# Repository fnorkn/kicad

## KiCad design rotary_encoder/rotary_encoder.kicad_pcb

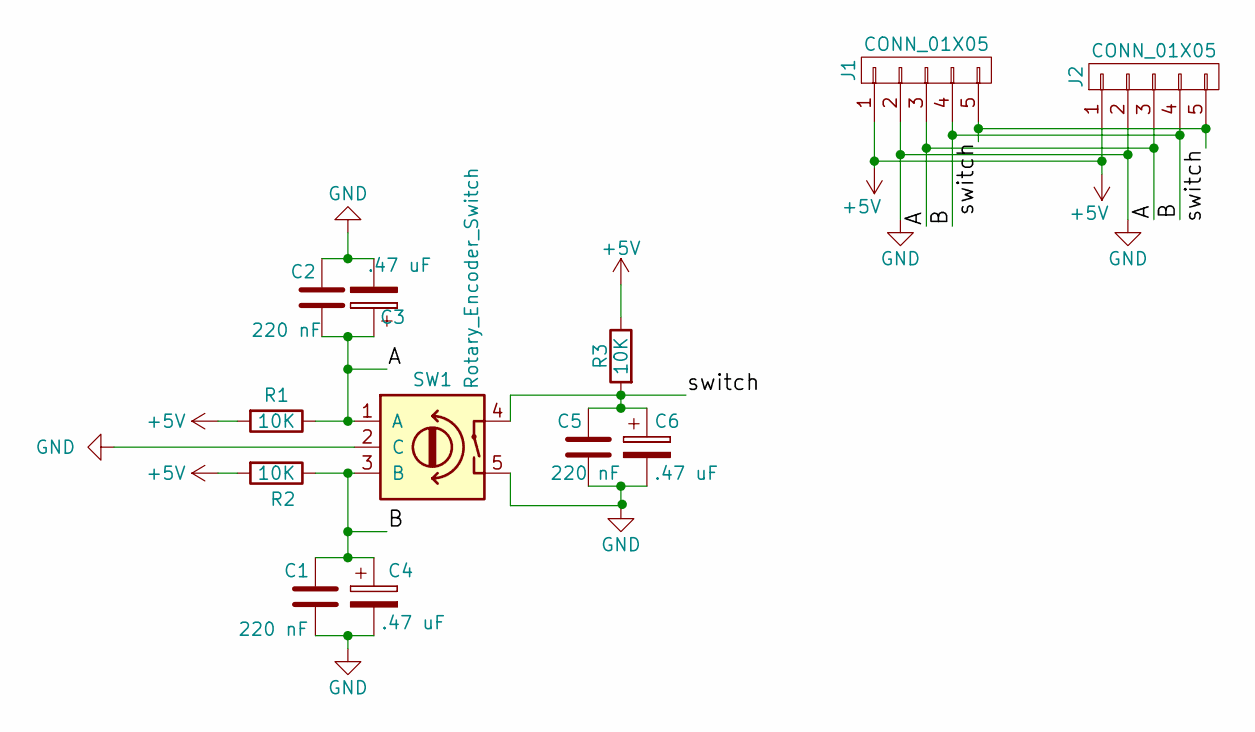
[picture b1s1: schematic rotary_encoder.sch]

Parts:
C1, C2, C5: 220 nF; C_0805_HandSoldering
C3, C4, C6: .47 uF; CP_Radial_D5.0mm_P2.00mm
J1, J2: CONN_01X05; Pin_Header_Straight_1x05_Pitch2.54mm
R1, R2, R3: 10K; R_0805_HandSoldering
SW1: Rotary_Encoder_Switch; rotary_encoder

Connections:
+5V: J1.1, J2.1, R1.2, R2.2, R3.1
/A: C2.2, C3.1, J1.3, J2.3, R1.1, SW1.1 (A)
/B: C1.1, C4.1, J1.4, J2.4, R2.1, SW1.3 (B)
/switch: C5.1, C6.1, J1.5, J2.5, R3.2, SW1.4
GND: C1.2, C2.1, C3.2, C4.2, C5.2, C6.2, J1.2, J2.2, SW1.2 (C), SW1.5

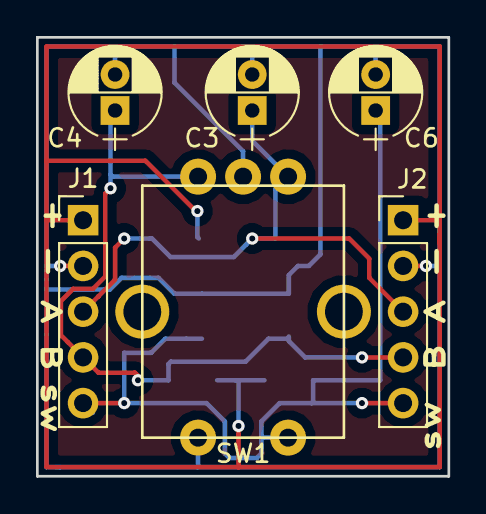
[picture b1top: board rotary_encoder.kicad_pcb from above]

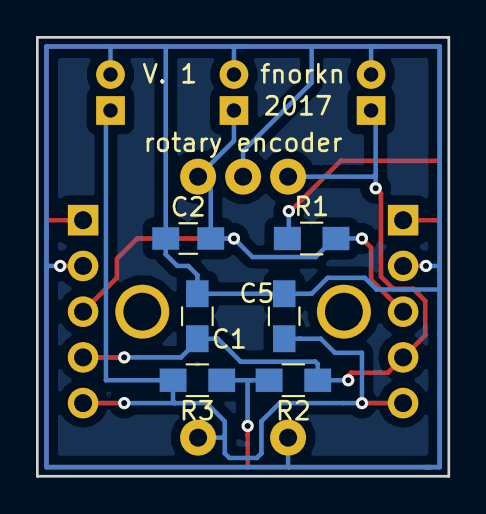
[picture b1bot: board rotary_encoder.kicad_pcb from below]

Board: 2 copper layers, 22.9 x 24.4 mm, 12 parts (6 on the bottom side), 5 nets.

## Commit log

2017-05-05 first version
